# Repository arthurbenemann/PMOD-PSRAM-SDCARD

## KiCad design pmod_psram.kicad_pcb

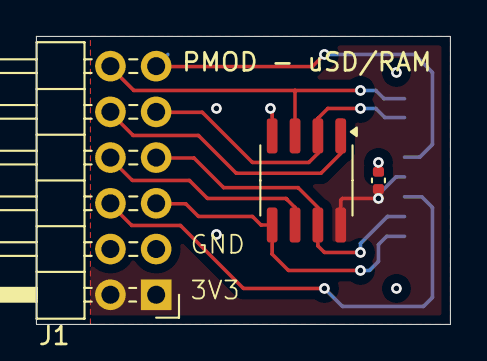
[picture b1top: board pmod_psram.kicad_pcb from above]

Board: 2 copper layers, 23.0 x 16.0 mm, 4 parts (1 on the bottom side), 10 nets.

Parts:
C1: C; C_0402_1005Metric
J1: Conn_02x06_Odd_Even; PinHeader_2x06_P2.54mm_Horizontal
J2: Micro_SD_Card_Det2; microSD_HC_Molex_104031-0811
U1: ESP-PSRAM64H; SOIC-8_3.9x4.9mm_P1.27mm

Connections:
+3.3V: C1.1, J1.1, J1.2, J2.4 (VDD), U1.8 (VCC)
/RAM_CE_B: J1.10, U1.1 (~CE)
/RAM_CLK: J1.8, U1.6 (SCLK)
/SD_CLK: J1.11, J2.5 (CLK)
/SD_CMD: J1.6, J2.3 (CMD)
/SIO0: J1.9, J2.7 (DAT0), U1.2 (SO/SIO)
/SIO1: J1.5, J2.1 (DAT2), U1.5 (SI/SIO)
/SIO2: J1.12, J2.8 (DAT1), U1.3 (SIO2)
/SIO3: J1.7, J2.2 (DAT3/CD), U1.7 (SIO3)
GND: C1.2, J1.3, J1.4, J2.6 (VSS), J2.9 (DET_B), J2.10 (DET_A), J2.11 (SHIELD), U1.4 (VSS)

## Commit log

2024-02-21 initial commit, rev01
